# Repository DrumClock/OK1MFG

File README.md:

# Ovládání rotátoru "SEVER"

# CW Paddle-Key

# Keypad - VHF log Tučňák

# PTT Sequencer

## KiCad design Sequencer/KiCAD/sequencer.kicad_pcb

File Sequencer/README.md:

# 5-WAY PTT Sequencer

Sequencer pro řízení postupného zapínání a vypínání jednotlivých částí zařízení.

# 🔴 [Arduino](https://github.com/DrumClock/OK1MFG/tree/main/Sequencer/Arduino/5CH_sequencer.ino) - program
Po aktivaci PTT sequencer postupně aktivuje jednotlivé výstupy s nastaveným časovým odstupem.

```text
PTT IN - ON

PTT 1 → PTT 2 → PTT 3 → PTT 4 → PTT  5
```

Po ukončení PTT proběhne vypnutí v opačném pořadí:

```text
PTT IN - OFF

PTT 5 → PTT 4 → PTT 3 → PTT 2 → PTT 1
```
Tím je zajištěno, že jednotlivé části zařízení jsou při přechodu mezi RX a TX zapínány a vypínány v definovaném pořadí.

# 🔴 Nastavení DELAY SEQ TIME

Časový odstup mezi jednotlivými kroky se nastavuje pomocí DIP přepínačů na spodní straně krabičky.
Nastavením kombinace přepínačů lze zvolit požadovanou rychlost sekvence podle použitého zařízení.

# 🔴 [KiCAD](https://github.com/DrumClock/OK1MFG/tree/main/Sequencer/KiCAD) - schéma kanálu LNA / PTT

# 🔴 Zadní panel

Na zadním panelu jsou umístěny vstupy a výstupy pro připojení zarizeni.

### PTT IN
Vstup pro ovládací PTT signál (šlapka proti GND).
Po aktivaci vstupu se spustí zapínací sekvence. 
Po jeho uvolnění proběhne vypínací sekvence v opačném pořadí.

###  PTT-TX
- RX je pin konektoru RCA ve stavu "otevřeného kolektoru" 
- TX je uzemněn pin konektoru RCA

### LNA 
- RX je přivedeno napájení 12V na pin 1 (+LNA RX) konektoru GX
- TX je je uzemněn pin 2 (PTT TX) konektoru GX

### 12V DC
Vstup napájení 12V DC / LNA 1 je společný i pro a elektroniku sequenceru.
Další vstupy DC napájí jen tento kanál LNA. ( na obrátku vstup 12V DC napájí jak elektroniku tak LNA 1 a 2 )

# 🔴 Přední panel

## Vypínač LNA 

Na předním panelu je samostatný vypínač, který
**odpojuje napájení pouze pro předzesilovače LNA**.
Nemá vliv na napájení ostatních částí zařízení.

## Indikace

LED indikace na předním panelu informuje o aktivním stavu RX/TX sekvence.
Během přechodu do TX a návratu do RX probíhá sekvence automaticky podle nastaveného časového kroku.

# 🔴 [FreeCAD](https://github.com/DrumClock/OK1MFG/tree/main/Sequencer/FreeCAD) - přední a zadní panel

Sequencer je umístěn v plastové krabičce KM60 159x60x140mm, prodejce [HADEX](https://www.hadex.cz/p/o208b-krabicka-plastova-km60-159x60x140mm?searchLogID=1625557)
,pokud by se již nevyráběla je ve složce soubor pro FreeCAD.

Přední a zadní panel k této krabičce je možné parametrovat v programu FreeCAD.

# 🔴 [Popisky](https://github.com/DrumClock/OK1MFG/tree/main/Sequencer/popisky) - samolepky ve formátu PDF, PNG, CDR (CorelDraw)

---

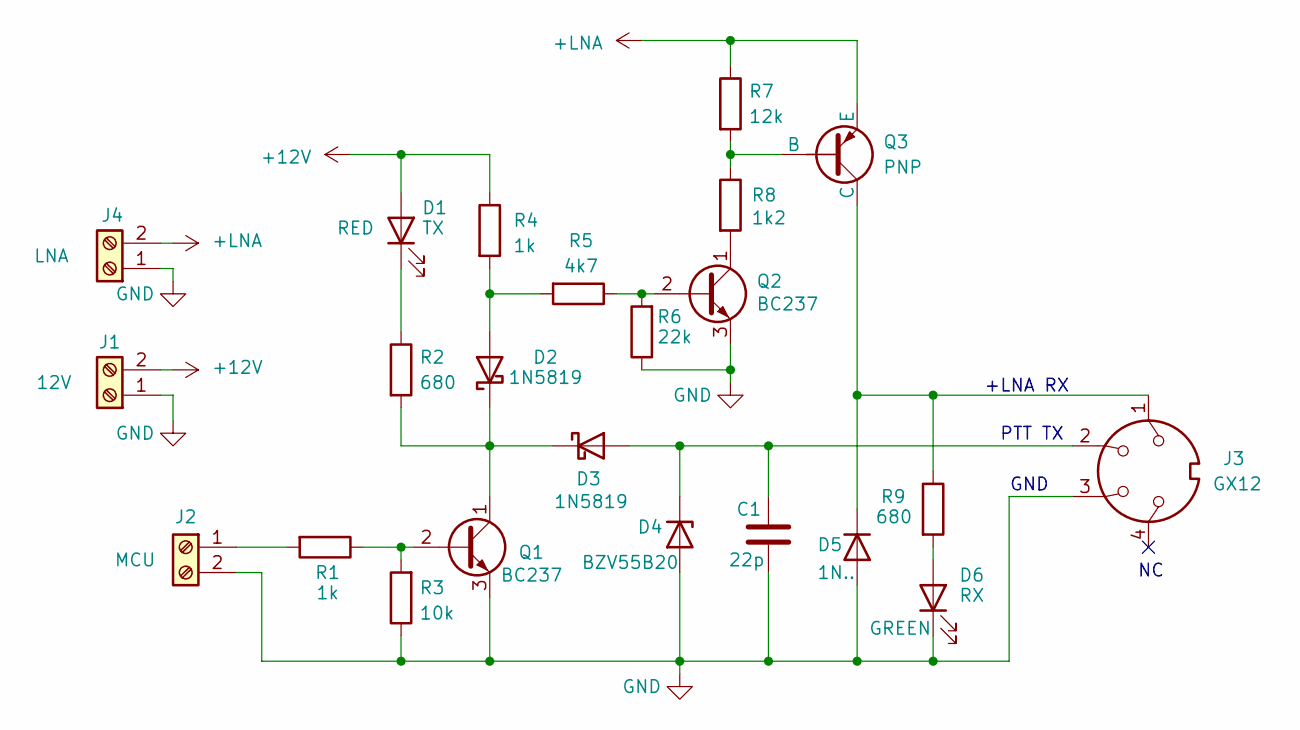
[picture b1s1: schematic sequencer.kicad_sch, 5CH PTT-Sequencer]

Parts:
C1: 22p; C_Disc_D7.5mm_W5.0mm_P7.50mm
D1: TX; LED_D3.0mm
D2, D3: 1N5819; D_DO-15_P10.16mm_Horizontal
D4: BZV55B20; D_5W_P10.16mm_Horizontal
D5: 1N..; D_5W_P10.16mm_Horizontal
D6: RX; LED_D3.0mm
J1: 12V; PinHeader_1x02_P2.54mm_Horizontal
J2: MCU; PinHeader_1x02_P2.54mm_Horizontal
J3: GX12; PinHeader_1x04_P2.54mm_Horizontal
J4: LNA; PinHeader_1x02_P2.54mm_Horizontal
Q1, Q2: BC237; TO-92L_HandSolder
Q3: PNP; TO-220-3_Vertical
R1, R4: 1k; R_Axial_DIN0207_L6.3mm_D2.5mm_P10.16mm_Horizontal
R2, R9: 680; R_Axial_DIN0207_L6.3mm_D2.5mm_P10.16mm_Horizontal
R3: 10k; R_Axial_DIN0207_L6.3mm_D2.5mm_P10.16mm_Horizontal
R5: 4k7; R_Axial_DIN0207_L6.3mm_D2.5mm_P10.16mm_Horizontal
R6: 22k; R_Axial_DIN0207_L6.3mm_D2.5mm_P10.16mm_Horizontal
R7: 12k; R_Axial_DIN0207_L6.3mm_D2.5mm_P10.16mm_Horizontal
R8: 1k2; R_Axial_DIN0207_L6.3mm_D2.5mm_P10.16mm_Horizontal

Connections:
+12V: D1.2 (A), J1.2, R4.1
+LNA: J4.2, Q3.3 (E), R7.1
GND: C1.2, D4.2 (A), D5.2 (A), D6.1 (K), J1.1, J2.2, J3.3, J4.1, Q1.3 (E), Q2.3 (E), R3.1, R6.1
unnamed: D1.1 (K), R2.1
unnamed: D2.2 (A), R4.2, R5.2
unnamed: D2.1 (K), D3.1 (K), Q1.1 (C), R2.2
unnamed: C1.1, D3.2 (A), D4.1 (K), J3.2
unnamed: D5.1 (K), J3.1, Q3.1 (C), R9.1
unnamed: D6.2 (A), R9.2
unnamed: J2.1, R1.2
unnamed: Q1.2 (B), R1.1, R3.2
unnamed: Q2.2 (B), R5.1, R6.2
unnamed: Q2.1 (C), R8.2
unnamed: Q3.2 (B), R7.2, R8.1

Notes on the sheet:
PTT TX
GND
+LNA RX

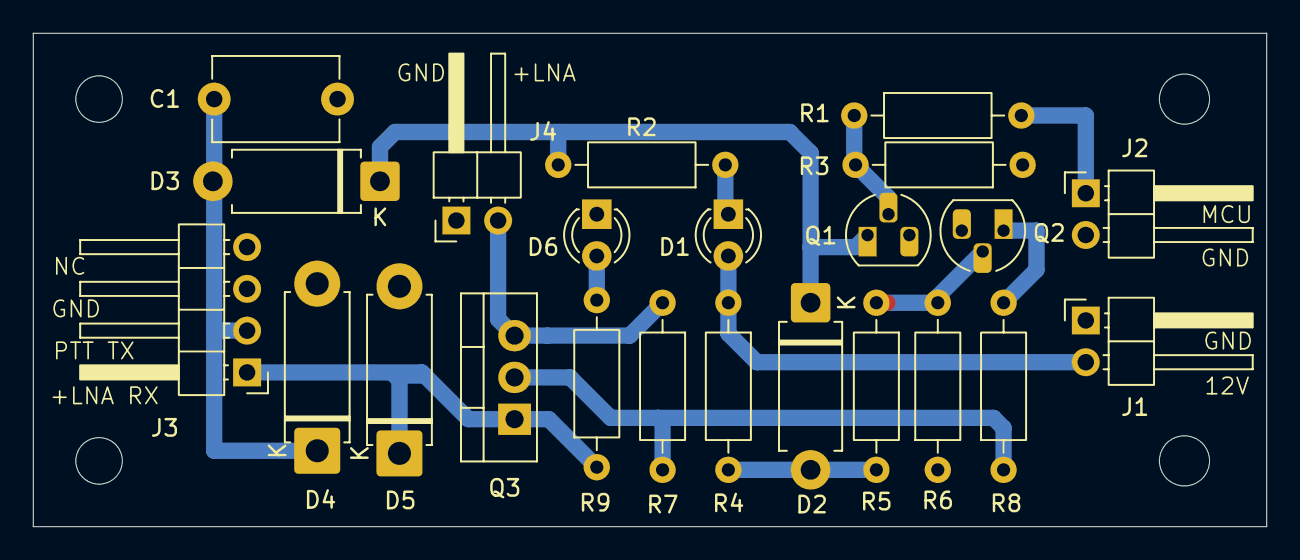
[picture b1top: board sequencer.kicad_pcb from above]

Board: 2 copper layers, 75.0 x 30.0 mm, 23 parts (0 on the bottom side), 14 nets.

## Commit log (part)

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2025-07-19 filtr
2026-03-14 14.3.26
    verze pro LED60
2026-03-14 14.3.26
2026-03-22 22.3.26
2026-03-27 27.3.26
2026-04-11 11.4.26
    AS5600
2026-04-11 11.4.26
2026-04-12 12.4.26
2026-04-19 19.4.26
2026-04-20 20.4.26
2026-05-09 9.5.26
2026-06-26 26.6.26
2026-06-30 30.6.26
